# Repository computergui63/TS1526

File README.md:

# TS1526
This is an open source derivative of the amazing OpenSpand project, designed to fit in a Timex Sinclair 1510 Case.

I've modified the design of the OpenSpand hardware specifically to fit in a Timex Sinclair 1510 modified case.  Some of the modifications includes the removal of the I2C IO and serial IO connections.  I've also replaced the UDA1334 with a MAX98357 chip.  This allows for a speaker to be included in the case powered by an amplifier.  I've also included a 3.5mm Phillips mono port to connect a mono speaker.   I've also eliminated the config button.  Config options are still available via the command options.  To better replicate the 1510, the SD card has moved to the "cartridge" and a cartridge port is provided.  The SD card slot was replaced with a microSD card.

This project is also open source as required via the GPL license.  You are free to modify my hardware as long as it's published as open source.

The Openspand project is published here: https://codeberg.org/NollKollTroll/OpenSpand

All software, manuals and binaries are available there.

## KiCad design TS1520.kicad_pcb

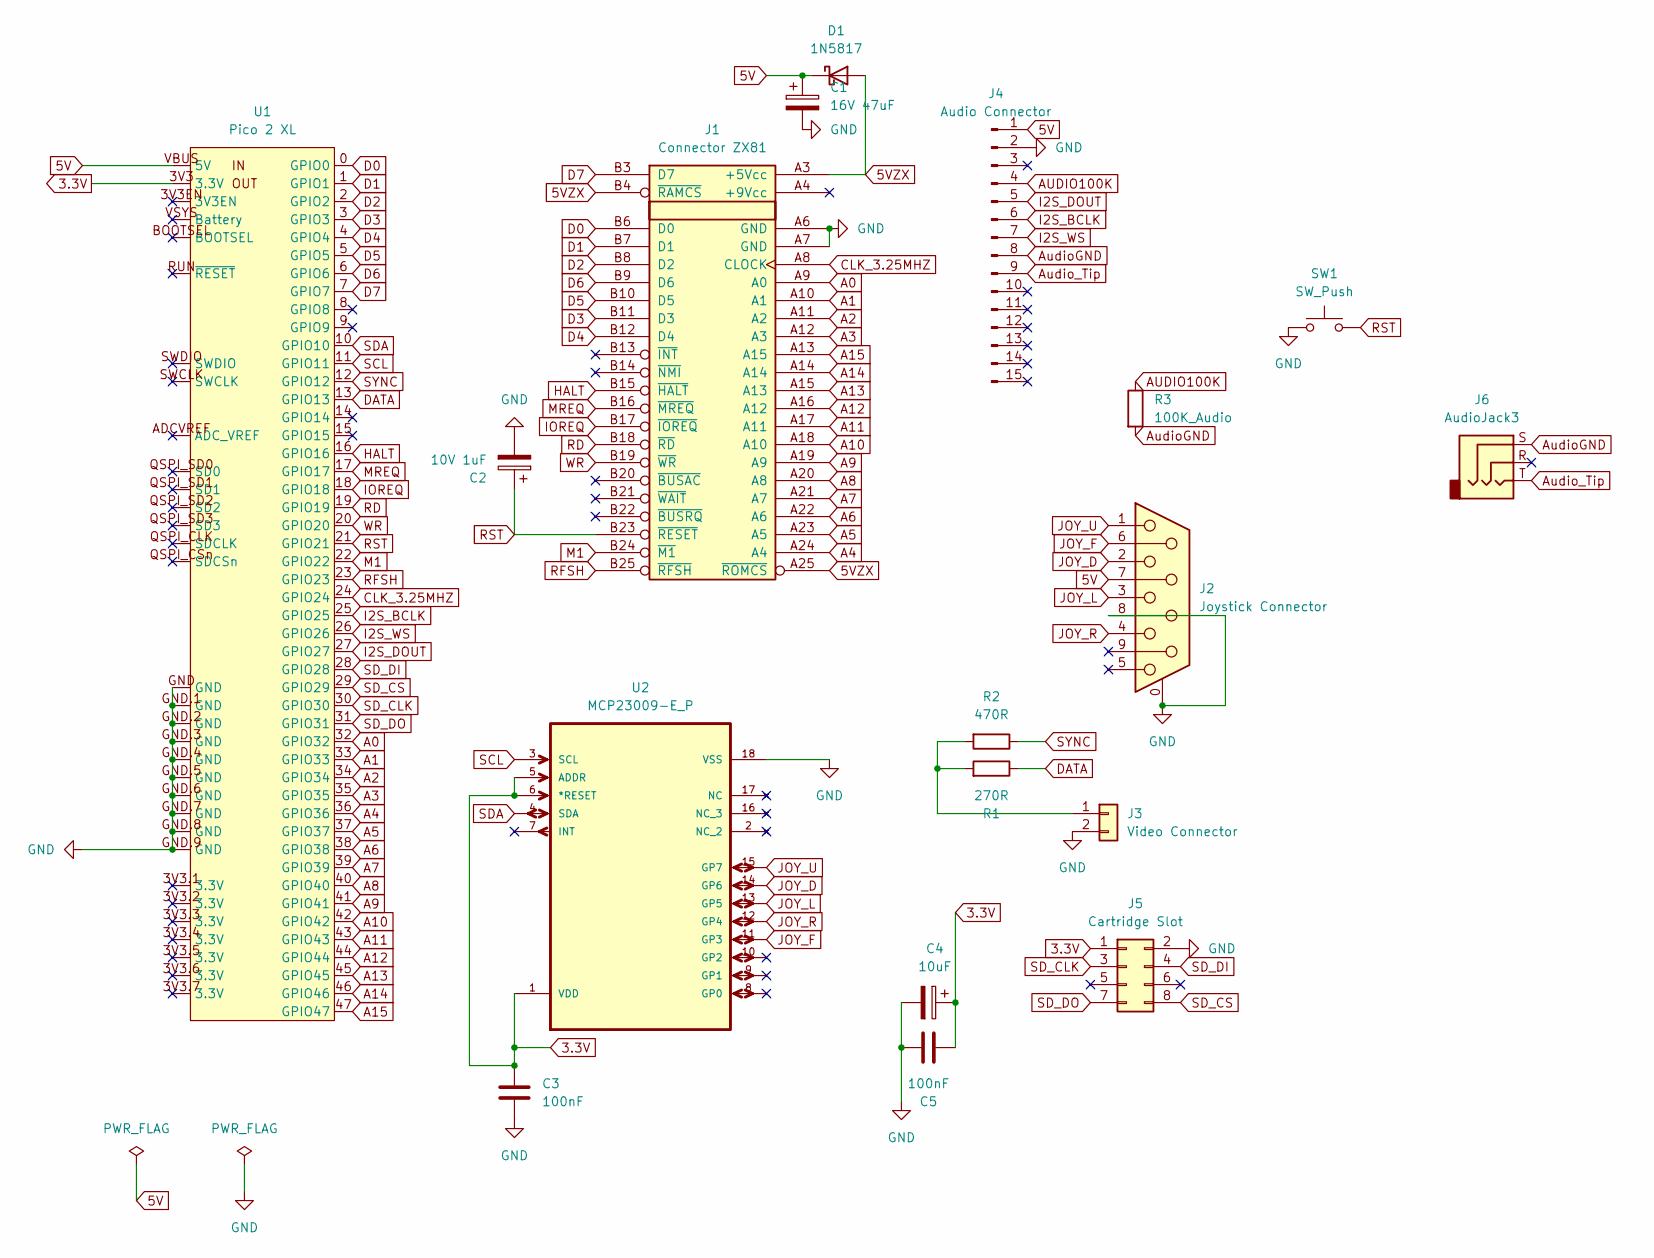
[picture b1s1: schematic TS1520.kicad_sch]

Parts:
C1: 16V 47uF; CP_Radial_D5.0mm_P2.50mm
C2: 10V 1uF; CP_Radial_D5.0mm_P2.50mm
C3, C5: 100nF; C_Disc_D3.0mm_W1.6mm_P2.50mm
C4: 10uF; CP_Radial_D5.0mm_P2.50mm
D1: 1N5817; D_DO-41_SOD81_P10.16mm_Horizontal
J1: Connector ZX81; EDGE ZX81 BOTTOM
J2: Joystick Connector; DSUB-9_Male_Horizontal_P2.77x2.84mm_EdgePinOffset4.94mm_Hou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
J3: Video Connector; ZX Video1
J4: Audio Connector; adafruit-MAX98357
J5: Cartridge Slot; EDGE ZX81 90_copy
J6: AudioJack3; PJ-307
R1: 270R; R_Axial_DIN0207_L6.3mm_D2.5mm_P10.16mm_Horizontal
R2: 470R; R_Axial_DIN0207_L6.3mm_D2.5mm_P10.16mm_Horizontal
R3: 100K_Audio; R_Axial_DIN0207_L6.3mm_D2.5mm_P10.16mm_Horizontal
SW1: SW_Push; SW_PUSH_6mm_H5mm
U1: Pico 2 XL; P2350Pico2XL
U2: MCP23009-E_P; M; MPN mcp23009-E/p; DigiKey_Part_Number MCP23009-E/P-ND

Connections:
3.3V: C3.1, C4.1, C5.2, J5.1, U1.3V3 (3.3V), U2.1 (VDD), U2.5 (ADDR), U2.6 (*RESET)
5V: C1.1, D1.1 (K), J2.7, J4.1, U1.VBUS (5V)
5VZX: D1.2 (A), J1.A3 (+5Vcc), J1.A25 (~ROMCS), J1.B4 (~RAMCS)
A0: J1.A9 (A0), U1.32 (GPIO32)
A1: J1.A10 (A1), U1.33 (GPIO33)
A2: J1.A11 (A2), U1.34 (GPIO34)
A3: J1.A12 (A3), U1.35 (GPIO35)
A4: J1.A24 (A4), U1.36 (GPIO36)
A5: J1.A23 (A5), U1.37 (GPIO37)
A6: J1.A22 (A6), U1.38 (GPIO38)
A7: J1.A21 (A7), U1.39 (GPIO39)
A8: J1.A20 (A8), U1.40 (GPIO40)
A9: J1.A19 (A9), U1.41 (GPIO41)
A10: J1.A18 (A10), U1.42 (GPIO42)
A11: J1.A17 (A11), U1.43 (GPIO43)
A12: J1.A16 (A12), U1.44 (GPIO44)
A13: J1.A15 (A13), U1.45 (GPIO45)
A14: J1.A14, U1.46 (GPIO46)
A15: J1.A13 (A15), U1.47 (GPIO47)
AUDIO100K: J4.4, R3.1
AudioGND: J4.8, J6.S, R3.2
Audio_Tip: J4.9, J6.T
CLK_3.25MHZ: J1.A8 (CLOCK), U1.24 (GPIO24)
D0: J1.B6 (D0), U1.0 (GPIO0)
D1: J1.B7 (D1), U1.1 (GPIO1)
D2: J1.B8 (D2), U1.2 (GPIO2)
D3: J1.B11 (D3), U1.3 (GPIO3)
D4: J1.B12 (D4), U1.4 (GPIO4)
D5: J1.B10 (D5), U1.5 (GPIO5)
D6: J1.B9 (D6), U1.6 (GPIO6)
D7: J1.B3 (D7), U1.7 (GPIO7)
DATA: R1.1, U1.13 (GPIO13)
GND: C1.2, C2.2, C3.2, C4.2, C5.1, J1.A6 (GND), J1.A7 (GND), J2.0 (PAD), J2.8, J3.2, J4.2, J5.2, SW1.1, U1.GND, U1.GND.1 (GND), U1.GND.2 (GND), U1.GND.3 (GND), U1.GND.4 (GND), U1.GND.5 (GND), U1.GND.6 (GND), U1.GND.7 (GND), U1.GND.8 (GND), U1.GND.9 (GND), U2.18 (VSS)
HALT: J1.B15 (~HALT), U1.16 (GPIO16)
I2S_BCLK: J4.6, U1.25 (GPIO25)
I2S_DOUT: J4.5, U1.27 (GPIO27)
I2S_WS: J4.7, U1.26 (GPIO26)
IOREQ: J1.B17 (~IOREQ), U1.18 (GPIO18)
JOY_D: J2.2, U2.14 (GP6)
JOY_F: J2.6, U2.11 (GP3)
JOY_L: J2.3, U2.13 (GP5)
JOY_R: J2.4, U2.12 (GP4)
JOY_U: J2.1, U2.15 (GP7)
M1: J1.B24 (~M1), U1.22 (GPIO22)
MREQ: J1.B16 (~MREQ), U1.17 (GPIO17)
unnamed: J3.1, R1.2, R2.2
RD: J1.B18 (~RD), U1.19 (GPIO19)
RFSH: J1.B25 (~RFSH), U1.23 (GPIO23)
RST: C2.1, J1.B23 (~RESET), SW1.2, U1.21 (GPIO21)
SCL: U1.11 (GPIO11), U2.3 (SCL)
SDA: U1.10 (GPIO10), U2.4 (SDA)
SD_CLK: J5.3, U1.30 (GPIO30)
SD_CS: J5.8, U1.29 (GPIO29)
SD_DI: J5.4, U1.28 (GPIO28)
SD_DO: J5.7, U1.31 (GPIO31)
SYNC: R2.1, U1.12 (GPIO12)
WR: J1.B19 (~WR), U1.20 (GPIO20)

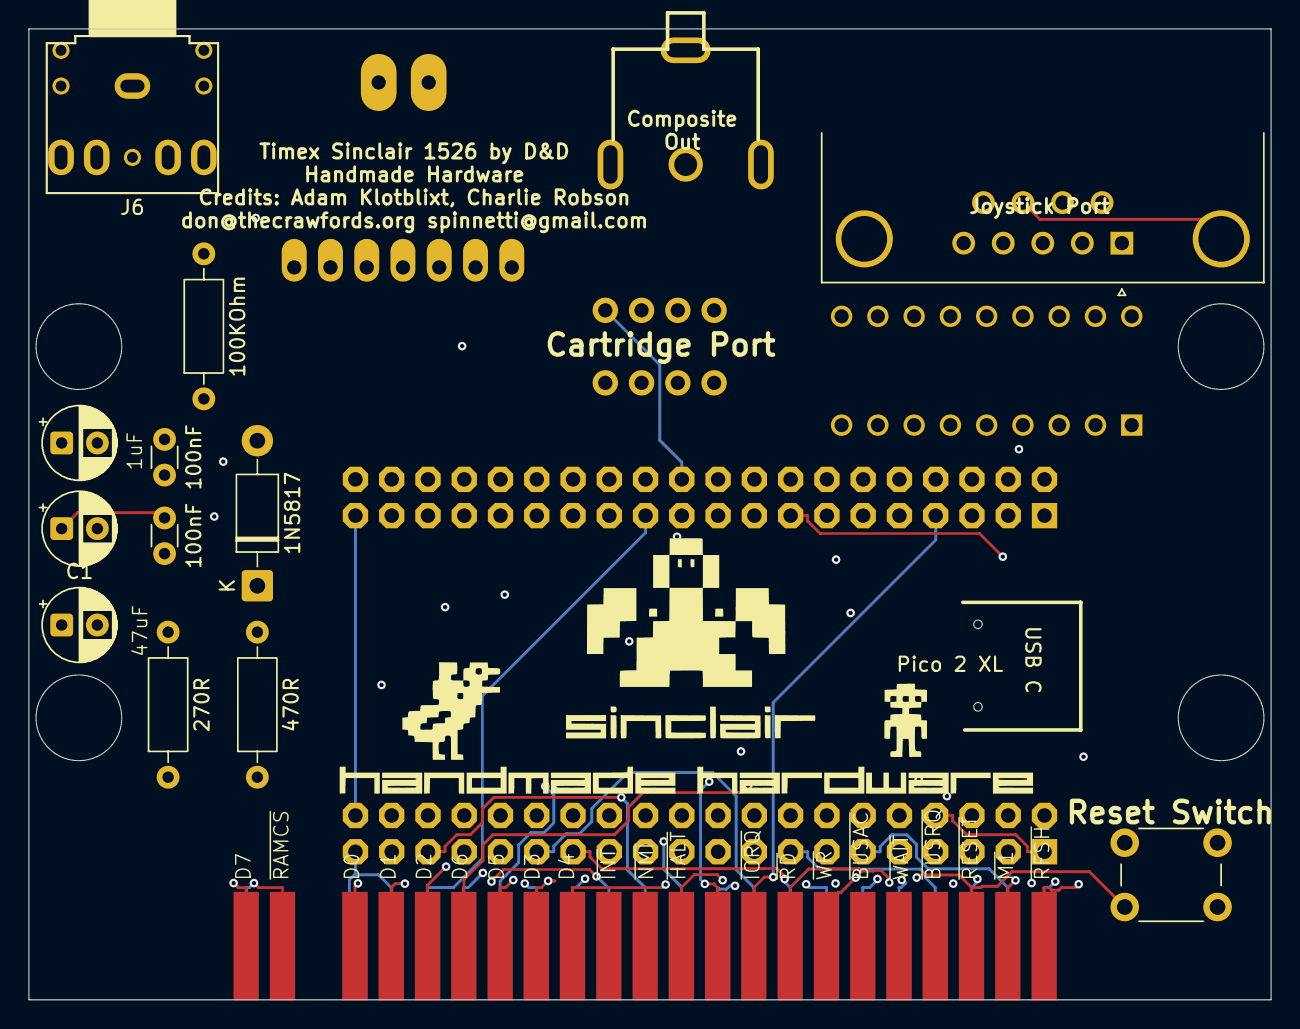
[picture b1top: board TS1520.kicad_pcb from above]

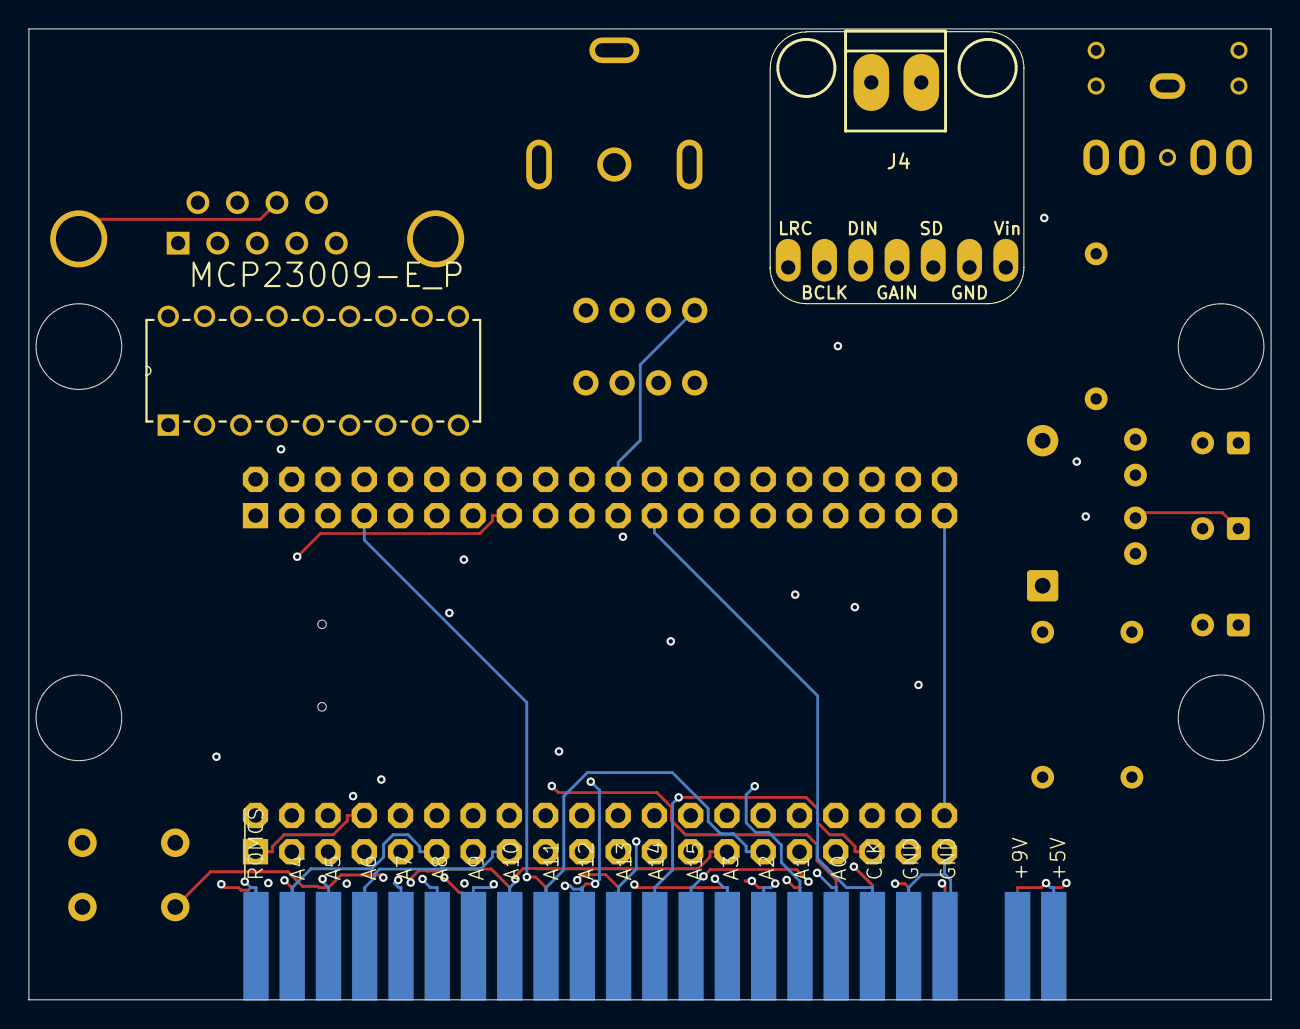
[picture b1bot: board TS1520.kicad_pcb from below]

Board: 4 copper layers, 87.0 x 68.0 mm, 18 parts (2 on the bottom side), 57 nets.

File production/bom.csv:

Designator,Footprint,Quantity,Value,LCSC Part #
C1,CP_Radial_D5.0mm_P2.50mm,1,16V 47uF,
C2,CP_Radial_D5.0mm_P2.50mm,1,10V 1uF,
"C3, C5",C_Disc_D3.0mm_W1.6mm_P2.50mm,2,100nF,
C4,CP_Radial_D5.0mm_P2.50mm,1,10uF,
D1,D_DO-41_SOD81_P10.16mm_Horizontal,1,1N5817,
J1,EDGE ZX81 BOTTOM,1,Connector ZX81,
J2,DSUB-9_Male_Horizontal_P2.77x2.84mm_EdgePinOffset4.94mm_Housed_MountingHolesOffset7.48mm,1,Joystick Connector,
J3,ZX Video1,1,Video Connector,
J4,adafruit-MAX98357,1,Audio Connector,
J5,EDGE ZX81 90_copy,1,Cartridge Slot,
J6,PJ-307,1,AudioJack3,
R1,R_Axial_DIN0207_L6.3mm_D2.5mm_P10.16mm_Horizontal,1,270R,
R2,R_Axial_DIN0207_L6.3mm_D2.5mm_P10.16mm_Horizontal,1,470R,
R3,R_Axial_DIN0207_L6.3mm_D2.5mm_P10.16mm_Horizontal,1,100KOhm,
SW1,SW_PUSH_6mm_H5mm,1,SW_Push,
U1,P2350Pico2XL,1,Pico 2 XL,
U2,M,1,MCP23009-E_P,mcp23009-E/p
